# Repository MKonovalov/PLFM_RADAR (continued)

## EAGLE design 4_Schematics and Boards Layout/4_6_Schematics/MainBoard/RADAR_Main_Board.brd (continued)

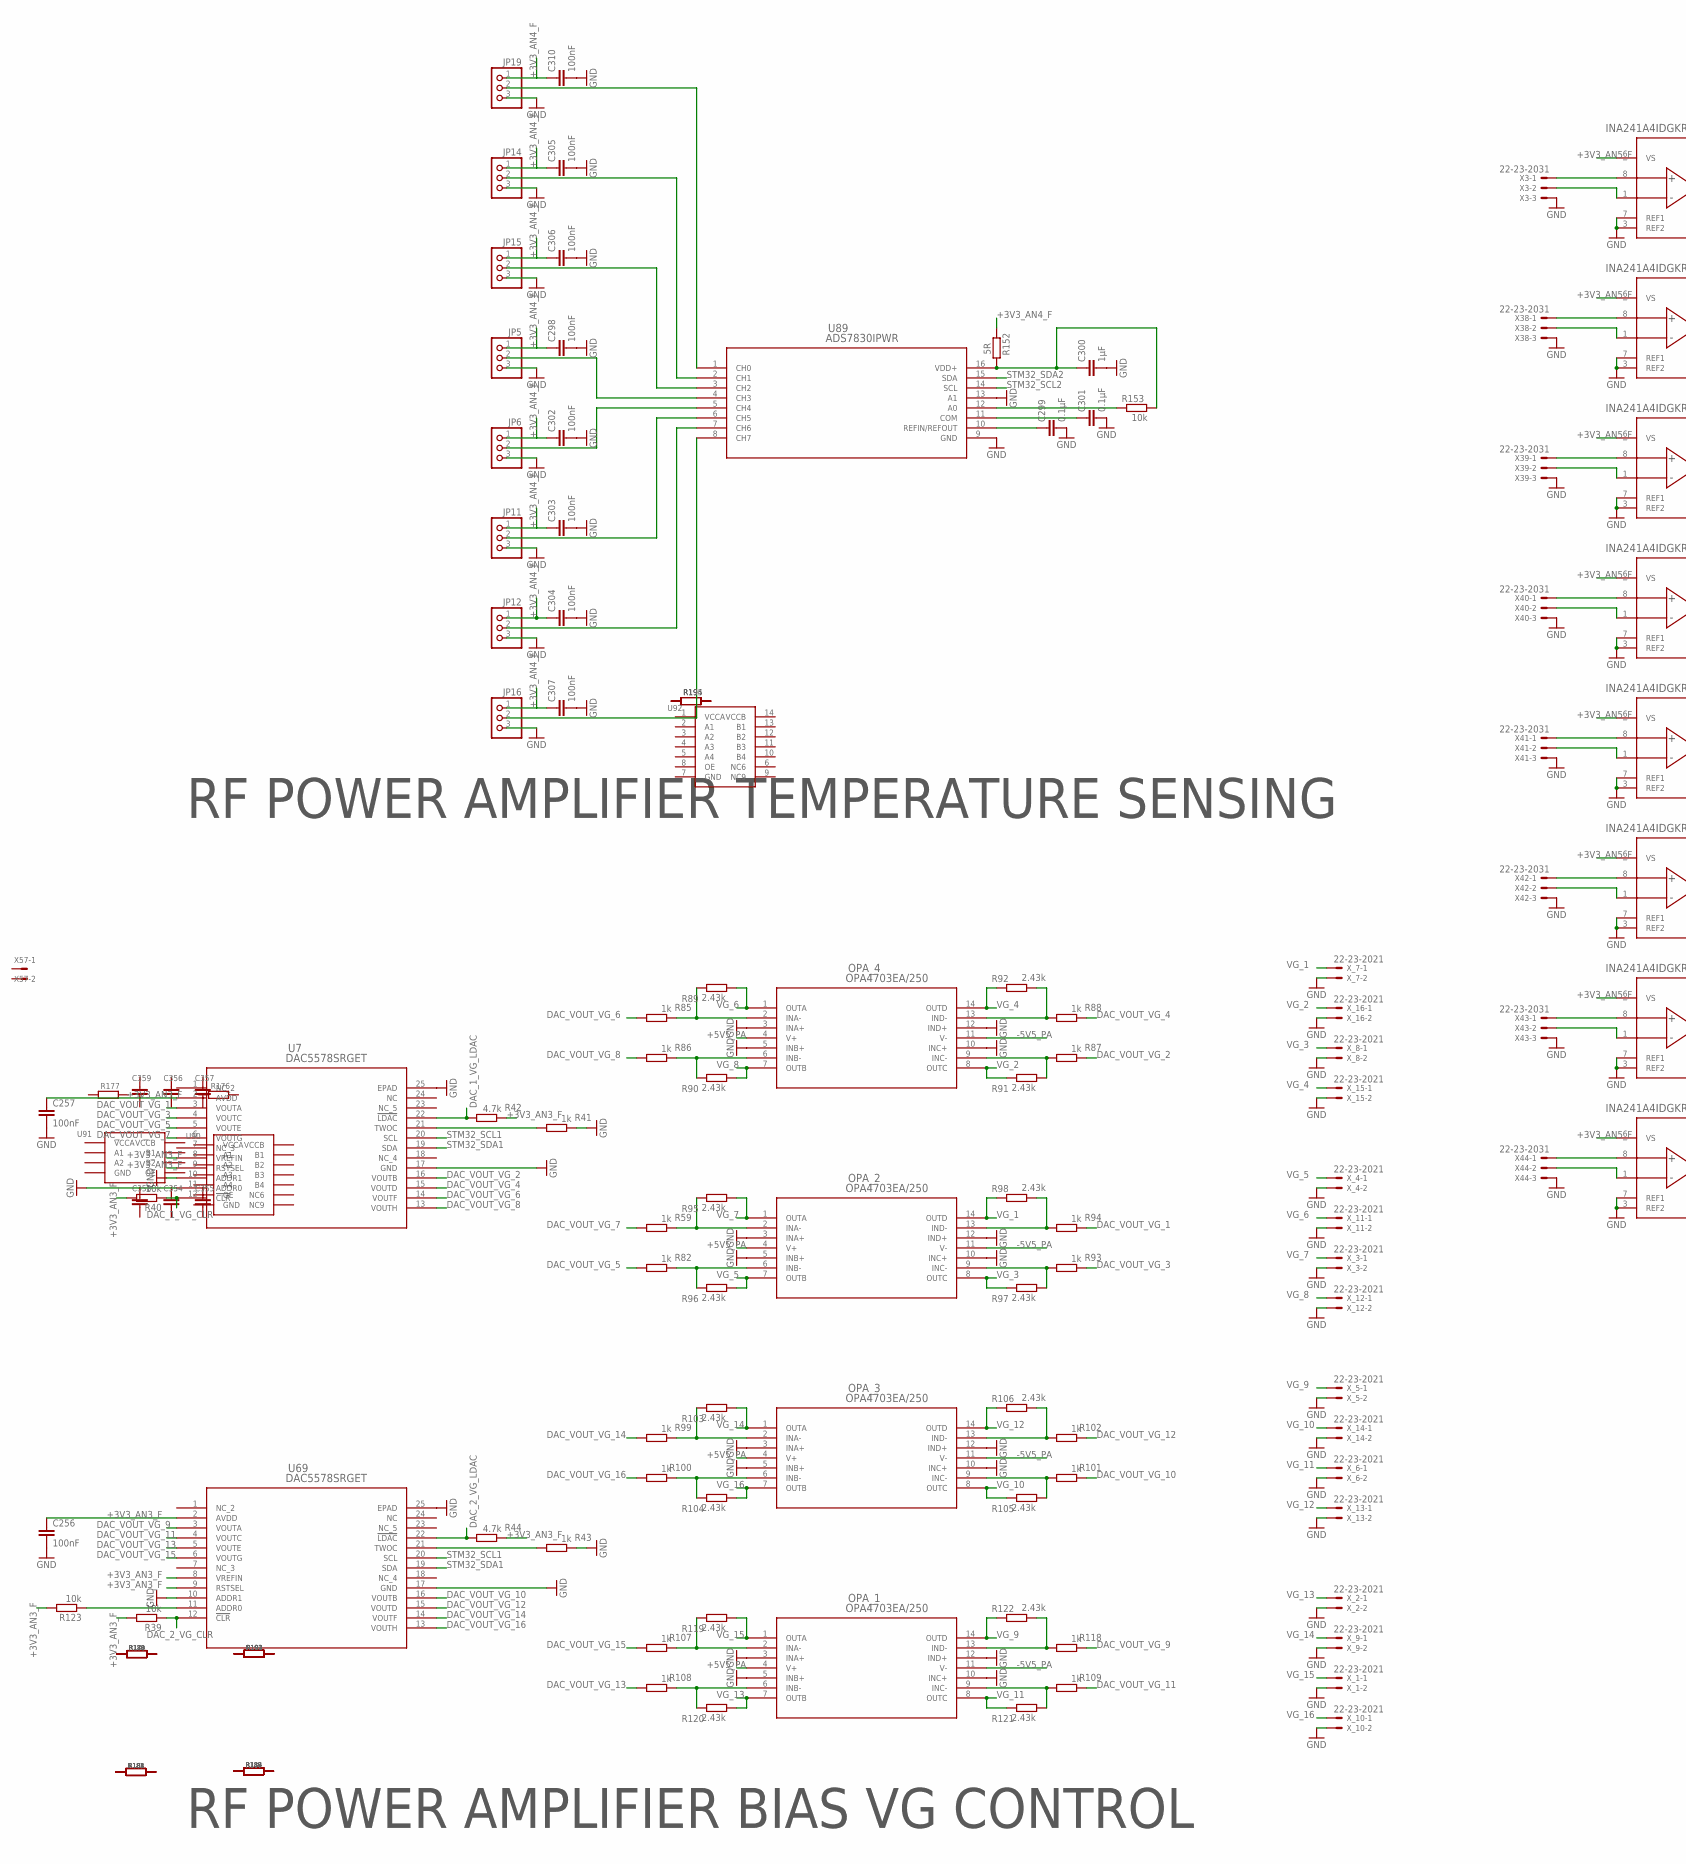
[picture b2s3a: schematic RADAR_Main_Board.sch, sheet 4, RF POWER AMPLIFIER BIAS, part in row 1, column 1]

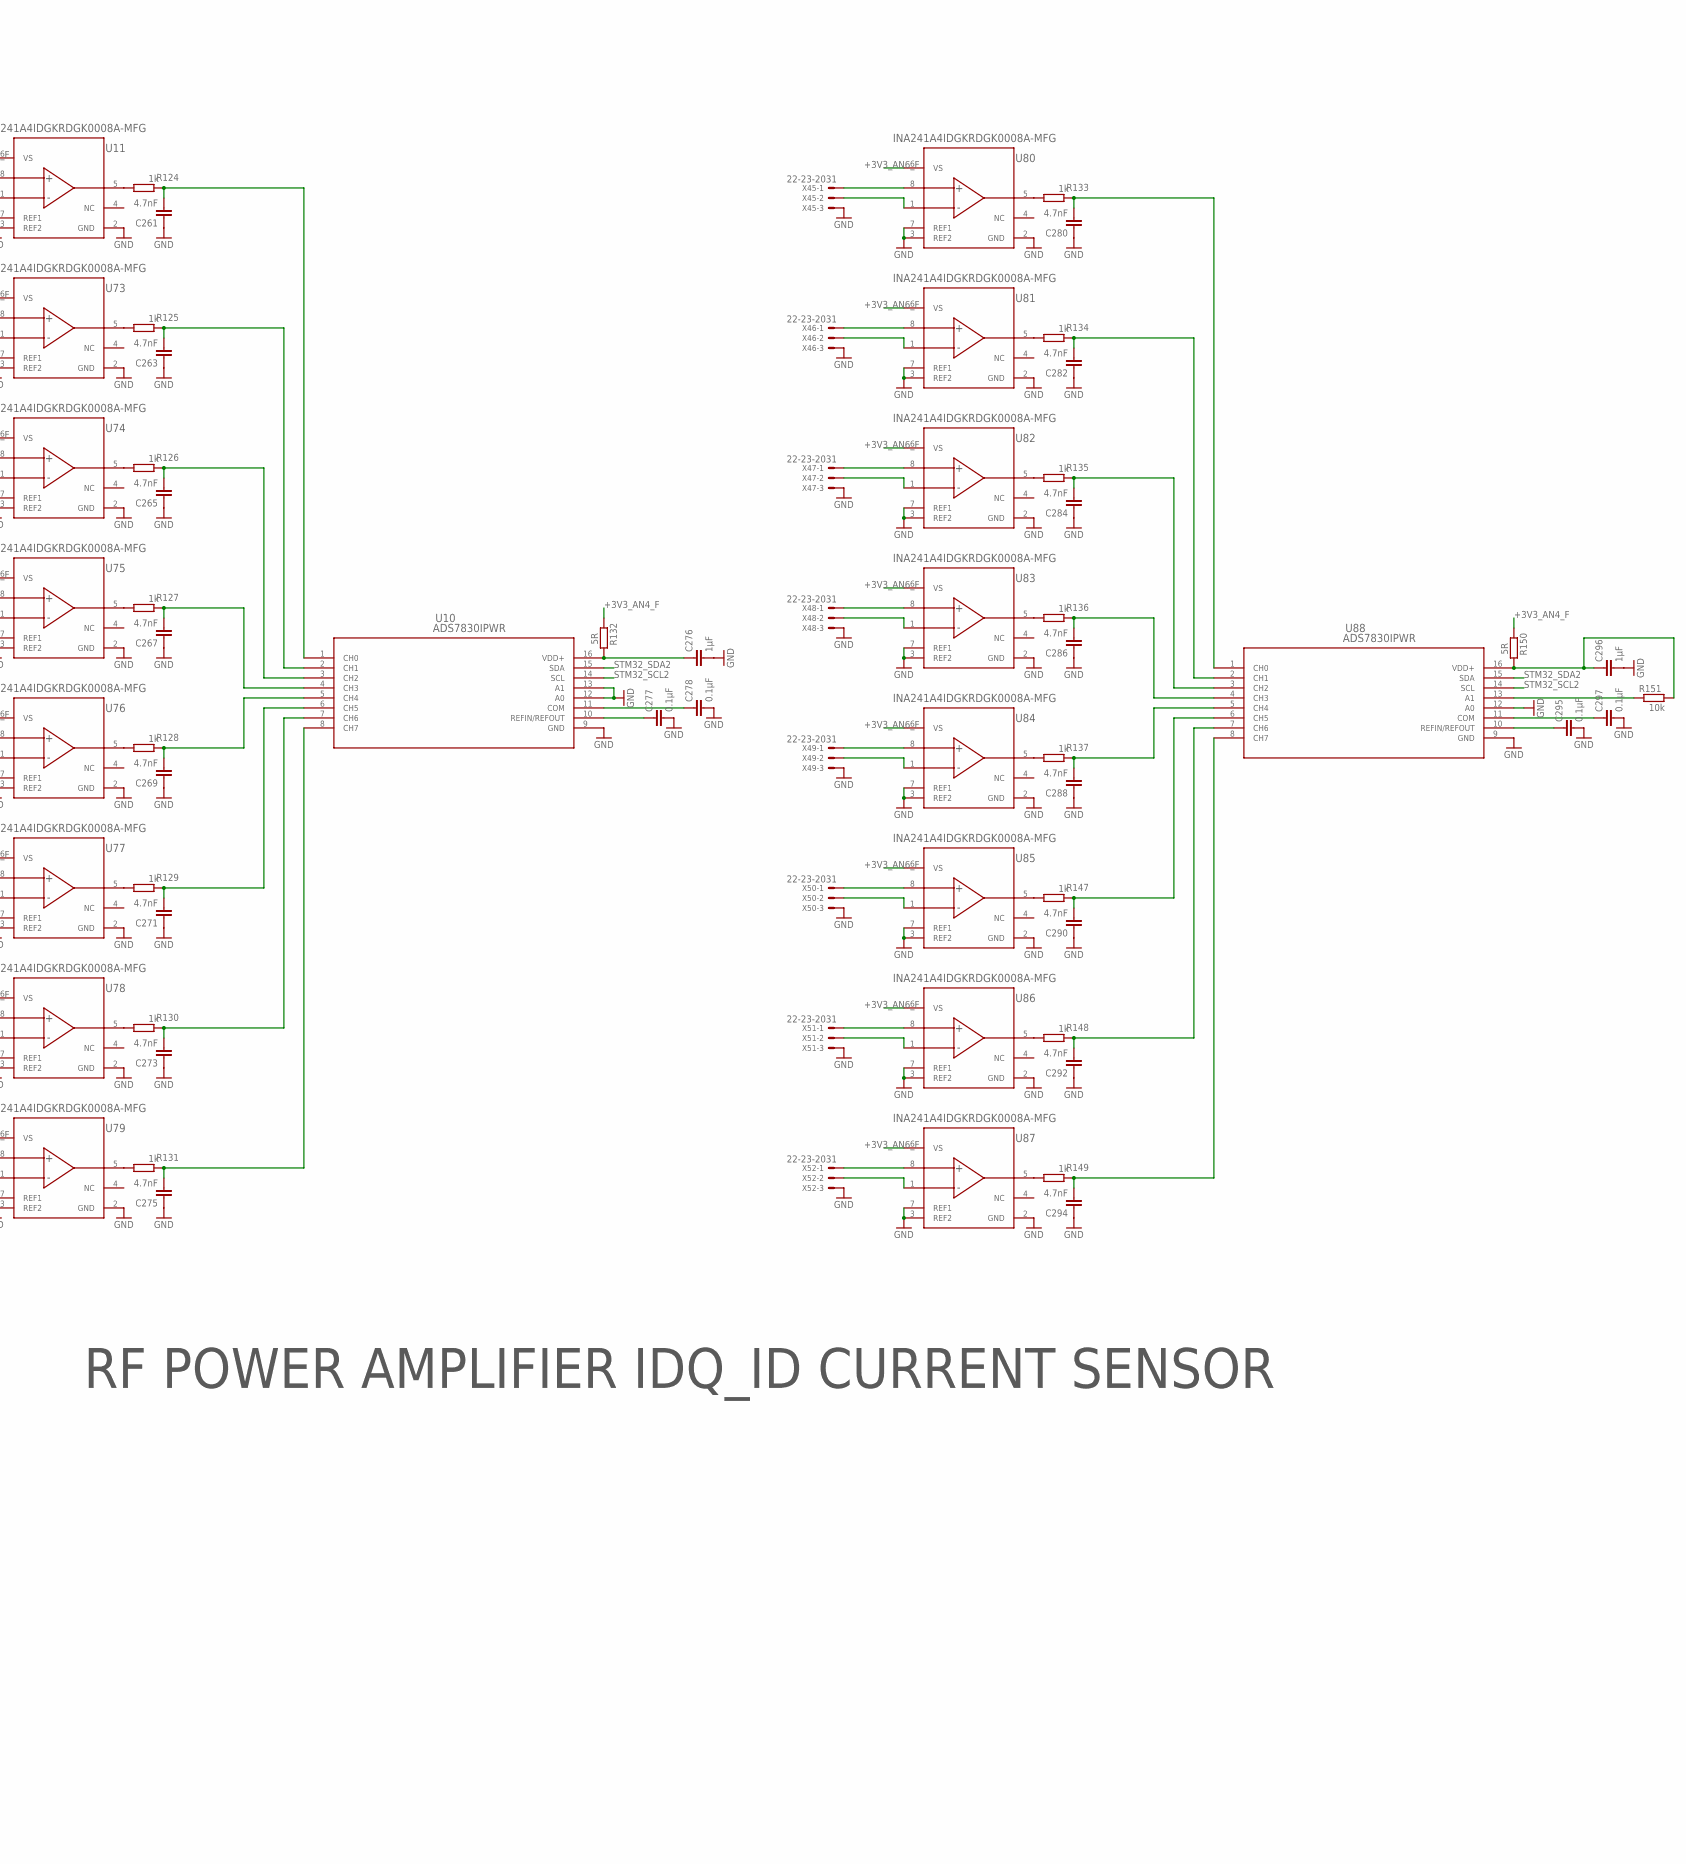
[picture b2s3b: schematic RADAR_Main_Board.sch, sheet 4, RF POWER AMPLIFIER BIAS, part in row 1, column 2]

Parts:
C256, C257, C298, C302, C303, C304, C305, C306, C307, C310: 100nF; C0201
C261, C263, C265, C267, C269, C271, C273, C275, C280, C282, C284, C286, C288, C290, C292, C294: 4.7nF; C0201
C276, C296, C300: 1µF; C0201
C277, C278, C295, C297, C299, C301: 0.1µF; C0201
C354, C355, C356, C357, C358, C359: 0.1uF; C0201
JP5, JP6, JP11, JP12, JP14, JP15, JP16, JP19: PINHD-1X3; 1X03
OPA_1, OPA_2, OPA_3, OPA_4: OPA4703EA/250; PW14
R39, R40, R123, R151, R153, R176, R177, R178, R179, R180, R181, R182, R183, R184, R185, R186, R187, R188, R189, R190, R191, R192, R193, R194: 10k; R0201
R41, R43, R59, R82, R85, R86, R87, R88, R93, R94, R99, R100, R101, R102, R107, R108, R109, R118, R124, R125, R126, R127, R128, R129, R130, R131, R133, R134, R135, R136, R137, R147, R148, R149: 1k; R0201
R42, R44, R195: 4.7k; R0201
R89, R90, R91, R92, R95, R96, R97, R98, R103, R104, R105, R106, R119, R120, R121, R122: 2.43k; R0201
R132, R150, R152: 5R; R0201
U7, U69: DAC5578SRGET; RGE24_2P7X2P7
U10, U88, U89: ADS7830IPWR; PW16
U11, U73, U74, U75, U76, U77, U78, U79, U80, U81, U82, U83, U84, U85, U86, U87: INA241A4IDGKRDGK0008A-MFG; DGK0008A-MFG
U92: TXS0104EPWR; PW0014A-MFG
X3, X38, X39, X40, X41, X42, X43, X44, X45, X46, X47, X48, X49, X50, X51, X52: 22-23-2031
X_1, X_2, X_3, X_4, X_5, X_6, X_7, X_8, X_9, X_10, X_11, X_12, X_13, X_14, X_15, X_16: 22-23-2021

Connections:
+1V8_FPGA: U92.VCCA; also elsewhere on the board
+3V3: U92.VCCB; also elsewhere on the board
+3V3_AN3_F: C256.1, C257.1, R39.2, R40.2, R42.1, R44.1, R123.2, U7.2 (AVDD), U7.8 (VREFIN), U7.9 (RSTSEL), U69.2 (AVDD), U69.8 (VREFIN), U69.9 (RSTSEL); also elsewhere on the board
+3V3_AN4_F: C298.1, C302.1, C303.1, C304.1, C305.1, C306.1, C307.1, C310.1, JP5.1, JP6.1, JP11.1, JP12.1, JP14.1, JP15.1, JP16.1, JP19.1, R132.1, R150.1, R152.1; also elsewhere on the board
+3V3_AN5_F: U11.6 (VS), U73.6 (VS), U74.6 (VS), U75.6 (VS), U76.6 (VS), U77.6 (VS), U78.6 (VS), U79.6 (VS); also elsewhere on the board
+3V3_AN6_F: U80.6 (VS), U81.6 (VS), U82.6 (VS), U83.6 (VS), U84.6 (VS), U85.6 (VS), U86.6 (VS), U87.6 (VS); also elsewhere on the board
+5V5_PA: OPA_1.4 (V+), OPA_2.4 (V+), OPA_3.4 (V+), OPA_4.4 (V+); also elsewhere on the board
ADC_SPI_CSB: U92.A1; also elsewhere on the board
ADC_SPI_SDIO: U92.A3; also elsewhere on the board
DAC_1_VG_CLR: R40.1, U7.12 (!CLR); also elsewhere on the board
DAC_1_VG_LDAC: R42.2, U7.22 (!LDAC); also elsewhere on the board
DAC_2_VG_CLR: R39.1, U69.12 (!CLR); also elsewhere on the board
DAC_2_VG_LDAC: R44.2, U69.22 (!LDAC); also elsewhere on the board
DAC_VOUT_VG_1: R94.1, U7.3 (VOUTA)
DAC_VOUT_VG_2: R87.1, U7.16 (VOUTB)
DAC_VOUT_VG_3: R93.1, U7.4 (VOUTC)
DAC_VOUT_VG_4: R88.1, U7.15 (VOUTD)
DAC_VOUT_VG_5: R82.2, U7.5 (VOUTE)
DAC_VOUT_VG_6: R85.2, U7.14 (VOUTF)
DAC_VOUT_VG_7: R59.2, U7.6 (VOUTG)
DAC_VOUT_VG_8: R86.2, U7.13 (VOUTH)
DAC_VOUT_VG_9: R118.1, U69.3 (VOUTA)
DAC_VOUT_VG_10: R101.1, U69.16 (VOUTB)
DAC_VOUT_VG_11: R109.1, U69.4 (VOUTC)
DAC_VOUT_VG_12: R102.1, U69.15 (VOUTD)
DAC_VOUT_VG_13: R108.2, U69.5 (VOUTE)
DAC_VOUT_VG_14: R99.2, U69.14 (VOUTF)
DAC_VOUT_VG_15: R107.2, U69.6 (VOUTG)
DAC_VOUT_VG_16: R100.2, U69.13 (VOUTH)
MCU_ADC_CSB: U92.B1; also elsewhere on the board
MCU_ADC_SCLK: U92.B2; also elsewhere on the board
MCU_ADC_SDIO: U92.B3; also elsewhere on the board
unnamed: R123.1, U69.11 (ADDR0)
unnamed: R43.2, U69.21 (TWOC)
unnamed: OPA_4.2 (INA-), R85.1, R89.1
unnamed: U11.8 (IN+), X3.1
unnamed: OPA_4.6 (INB-), R86.1, R90.1
unnamed: U11.1 (IN-), X3.2
unnamed: R124.2, U11.5 (OUT)
unnamed: C261.2, R124.1, U10.1 (CH0)
unnamed: U73.8 (IN+), X38.1
unnamed: OPA_4.9 (INC-), R87.2, R91.2
unnamed: U73.1 (IN-), X38.2
unnamed: R125.2, U73.5 (OUT)
unnamed: OPA_4.13 (IND-), R88.2, R92.2
unnamed: C263.2, R125.1, U10.2 (CH1)
unnamed: U74.8 (IN+), X39.1
unnamed: U74.1 (IN-), X39.2
unnamed: R126.2, U74.5 (OUT)
unnamed: R41.2, U7.21 (TWOC)
unnamed: OPA_2.2 (INA-), R59.1, R95.1
unnamed: C265.2, R126.1, U10.3 (CH2)
unnamed: OPA_2.6 (INB-), R82.1, R96.1
unnamed: U75.8 (IN+), X40.1
unnamed: U75.1 (IN-), X40.2
unnamed: R127.2, U75.5 (OUT)
unnamed: OPA_2.9 (INC-), R93.2, R97.2
unnamed: C267.2, R127.1, U10.4 (CH3)
unnamed: U76.8 (IN+), X41.1
unnamed: OPA_2.13 (IND-), R94.2, R98.2
unnamed: U76.1 (IN-), X41.2
unnamed: R128.2, U76.5 (OUT)
unnamed: C269.2, R128.1, U10.5 (CH4)
unnamed: U77.8 (IN+), X42.1
unnamed: U77.1 (IN-), X42.2
unnamed: R129.2, U77.5 (OUT)
unnamed: OPA_3.2 (INA-), R99.1, R103.1
unnamed: C271.2, R129.1, U10.6 (CH5)
unnamed: OPA_3.6 (INB-), R100.1, R104.1
unnamed: U78.8 (IN+), X43.1
unnamed: U78.1 (IN-), X43.2
unnamed: R130.2, U78.5 (OUT)
unnamed: OPA_3.9 (INC-), R101.2, R105.2
unnamed: C273.2, R130.1, U10.7 (CH6)
unnamed: U79.8 (IN+), X44.1
unnamed: OPA_3.13 (IND-), R102.2, R106.2
unnamed: U79.1 (IN-), X44.2
unnamed: R131.2, U79.5 (OUT)
unnamed: C275.2, R131.1, U10.8 (CH7)
unnamed: C277.1, U10.10 (REFIN/REFOUT)
unnamed: C276.1, R132.2, U10.16 (VDD+)
unnamed: C278.1, U10.11 (COM)
unnamed: OPA_1.2 (INA-), R107.1, R119.1
unnamed: U80.8 (IN+), X45.1
unnamed: OPA_1.6 (INB-), R108.1, R120.1
unnamed: U80.1 (IN-), X45.2
unnamed: R133.2, U80.5 (OUT)
unnamed: C280.2, R133.1, U88.1 (CH0)
unnamed: OPA_1.9 (INC-), R109.2, R121.2
unnamed: U81.8 (IN+), X46.1
unnamed: U81.1 (IN-), X46.2
unnamed: OPA_1.13 (IND-), R118.2, R122.2
unnamed: R134.2, U81.5 (OUT)
unnamed: C282.2, R134.1, U88.2 (CH1)
unnamed: U82.8 (IN+), X47.1
unnamed: U82.1 (IN-), X47.2
unnamed: R135.2, U82.5 (OUT)
unnamed: C284.2, R135.1, U88.3 (CH2)
unnamed: U83.8 (IN+), X48.1
unnamed: U83.1 (IN-), X48.2
unnamed: R136.2, U83.5 (OUT)
unnamed: C286.2, R136.1, U88.4 (CH3)
unnamed: U84.8 (IN+), X49.1
unnamed: U84.1 (IN-), X49.2
unnamed: R137.2, U84.5 (OUT)
unnamed: C288.2, R137.1, U88.5 (CH4)
unnamed: U85.8 (IN+), X50.1
unnamed: U85.1 (IN-), X50.2
unnamed: R147.2, U85.5 (OUT)
unnamed: C290.2, R147.1, U88.6 (CH5)
unnamed: U86.8 (IN+), X51.1
unnamed: U86.1 (IN-), X51.2
unnamed: R148.2, U86.5 (OUT)
unnamed: C292.2, R148.1, U88.7 (CH6)
unnamed: U87.8 (IN+), X52.1
unnamed: U87.1 (IN-), X52.2
unnamed: R149.2, U87.5 (OUT)
unnamed: C294.2, R149.1, U88.8 (CH7)
unnamed: C295.1, U88.10 (REFIN/REFOUT)
unnamed: C296.1, R150.2, R151.2, U88.16 (VDD+)
unnamed: C297.1, U88.11 (COM)
unnamed: R151.1, U88.13 (A1)
unnamed: R153.1, U89.12 (A0)
unnamed: C299.1, U89.10 (REFIN/REFOUT)
unnamed: C300.1, R152.2, R153.2, U89.16 (VDD+)
unnamed: C301.1, U89.11 (COM)
N$U92_OE: U92.OE; also elsewhere on the board
STM32_SCL1: U7.20 (SCL), U69.20 (SCL); also elsewhere on the board
STM32_SCL2: U10.14 (SCL), U88.14 (SCL), U89.14 (SCL); also elsewhere on the board
STM32_SDA1: U7.19 (SDA), U69.19 (SDA); also elsewhere on the board
STM32_SDA2: U10.15 (SDA), U88.15 (SDA), U89.15 (SDA); also elsewhere on the board
TEMP_1: JP19.2, U89.1 (CH0); also elsewhere on the board
TEMP_2: JP14.2, U89.2 (CH1); also elsewhere on the board
TEMP_3: JP15.2, U89.3 (CH2); also elsewhere on the board
TEMP_4: JP5.2, U89.4 (CH3); also elsewhere on the board
TEMP_5: JP6.2, U89.5 (CH4); also elsewhere on the board
TEMP_6: JP11.2, U89.6 (CH5); also elsewhere on the board
TEMP_7: JP12.2, U89.7 (CH6); also elsewhere on the board
TEMP_8: JP16.2, U89.8 (CH7); also elsewhere on the board
VG_1: OPA_2.14 (OUTD), R98.1, R178.1, X_7.1
VG_2: OPA_4.8 (OUTC), R91.1, R190.1, X_16.1
VG_3: OPA_2.8 (OUTC), R97.1, R179.1, X_8.1
VG_4: OPA_4.14 (OUTD), R92.1, R191.1, X_15.1
VG_5: OPA_2.7 (OUTB), R96.2, R180.1, X_4.1
VG_6: OPA_4.1 (OUTA), R89.2, R192.1, X_11.1
VG_7: OPA_2.1 (OUTA), R95.2, R181.1, X_3.1
VG_8: OPA_4.7 (OUTB), R90.2, R193.1, X_12.1
VG_9: OPA_1.14 (OUTD), R122.1, R182.1, X_5.1
VG_10: OPA_3.8 (OUTC), R105.1, R186.1, X_14.1
VG_11: OPA_1.8 (OUTC), R121.1, R183.1, X_6.1
VG_12: OPA_3.14 (OUTD), R106.1, R187.1, X_13.1
VG_13: OPA_1.7 (OUTB), R120.2, R184.1, X_2.1
VG_14: OPA_3.1 (OUTA), R103.2, R188.1, X_9.1
VG_15: OPA_1.1 (OUTA), R119.2, R185.1, X_1.1
VG_16: OPA_3.7 (OUTB), R104.2, R189.1, X_10.1

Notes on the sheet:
RF POWER AMPLIFIER IDQ_ID CURRENT SENSOR
RF POWER AMPLIFIER BIAS VG CONTROL
RF POWER AMPLIFIER TEMPERATURE SENSING

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
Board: 10 copper layers, 836 parts (0 on the bottom side), 668 nets.

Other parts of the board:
R196, R197, R198, R199, R200, R201, R202, R203: 10k; R0201
U90: TXS0104EPWR; PW0014A-MFG
U91: TXS0102DCUR; DCU0008A-MFG
X5, X7, X14: 22-23-2041
X6, X11, X13, X15, X19, X22: 22-23-2031
X25, X26, X27, X57: 22-23-2021

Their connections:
+2V5_FPGA: U90.1, U91.3, X57.1; also elsewhere on the board
+3V3_AN4_F: R196.2, R197.2, R198.2, R199.2, R200.2, R201.2, R202.2, R203.2; also elsewhere on the board
+3V3_FPGA: U90.14, U91.7; also elsewhere on the board
+5V0_PA_1: X14.1; also elsewhere on the board
+5V0_PA_2: X5.1; also elsewhere on the board
+5V0_PA_3: X7.1; also elsewhere on the board
-3V3_SW: X6.1; also elsewhere on the board
-3V4: X11.1, X22.1; also elsewhere on the board
-5V0_ADAR12: X13.1; also elsewhere on the board
-5V0_ADAR34: X15.1; also elsewhere on the board
-5V5_PA: X19.1; also elsewhere on the board
FLASH_DQ0_F: U90.13; also elsewhere on the board
FLASH_DQ1_F: U90.12; also elsewhere on the board
FLASH_DQ2_F: U90.11; also elsewhere on the board
FLASH_DQ3_F: U90.10; also elsewhere on the board
FLASH_NCS_F: U91.8; also elsewhere on the board
FLASH_NRST_F: U91.1; also elsewhere on the board
FPGA_FLASH_DQ0: U90.2; also elsewhere on the board
FPGA_FLASH_DQ1: U90.3; also elsewhere on the board
FPGA_FLASH_DQ2: U90.4; also elsewhere on the board
FPGA_FLASH_DQ3: U90.5; also elsewhere on the board
FPGA_FLASH_NCS: U91.5; also elsewhere on the board
FPGA_FLASH_NRST: U91.4; also elsewhere on the board
N$U90_OE: U90.8; also elsewhere on the board
N$U91_OE: U91.6; also elsewhere on the board
PG_2V5_FPGA: X27.1; also elsewhere on the board
PG_3V3_ADTR: X25.1; also elsewhere on the board
PG_3V3_XO: X26.1; also elsewhere on the board
TEMP_1: R196.1; also elsewhere on the board
TEMP_2: R197.1; also elsewhere on the board
TEMP_3: R198.1; also elsewhere on the board
TEMP_4: R199.1; also elsewhere on the board
TEMP_5: R200.1; also elsewhere on the board
TEMP_6: R201.1; also elsewhere on the board
TEMP_7: R202.1; also elsewhere on the board
TEMP_8: R203.1; also elsewhere on the board

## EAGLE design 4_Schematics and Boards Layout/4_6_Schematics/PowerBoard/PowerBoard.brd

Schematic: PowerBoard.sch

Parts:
C1, C6, C12, C18, C29, C30, C36, C42, C54, C60, C66, C71, C76, C77, C83, C89, C109, C119, C129, C144, C154: 0.1µF; C0805
C2, C3, C7, C8, C11, C13, C14, C17, C19, C20, C23, C31, C32, C35, C37, C38, C41, C43, C44, C47, C48, C49, C55, C56, C59, C61, C62, C65, C67, C68, C72, C73, C78, C79, C82, C84, C85, C88, C90, C91, C110, C111, C120, C121, C130, C131, C145, C146, C149, C155, C156, C159, C164, C165, C169, C170, C171, C172: 22µF; C0603
C4, C5, C9, C10, C15, C16, C21, C22, C24, C25, C28, C33, C34, C39, C40, C45, C46, C50, C51, C52, C53, C57, C58, C63, C64, C69, C70, C74, C75, C80, C81, C86, C87, C92, C93, C94, C95, C108, C112, C113, C114, C115, C118, C122, C123, C124, C125, C128, C132, C133, C134, C135, C138, C139, C140, C143, C147, C148, C157, C158: 10µF; C0805
C26, C27, C106, C107, C116, C117, C126, C127, C136, C137, C141, C142: 1µF; C0805
C96, C97, C98, C99, C100, C101, C102, C103, C104, C105, C173, C174: T521W476M020ATE045; T521W
C150, C152, C160, C162, C167, C168: 10nF; C0603
C151, C153, C161, C163, C166: 10µF; C0603
R1: 3.09k; M0805
R2, R4, R6, R8, R10, R12, R14, R16, R18, R20, R22, R24, R26, R28, R30, R32, R34, R36, R38, R40, R42, R44, R46, R48, R50, R52, R56, R61, R62, R63: 10k; M0805
R3: 13.7k; M0805
R5, R7, R11, R13, R15, R19: 32.2k; M0805
R9, R35, R43, R47: 12k; M0805
R17, R23, R25, R27, R29, R31, R37, R41, R45, R51, R55: 56.2k; M0805
R21: 34.8k; M0805
R33: 61.9k; M0805
R39: 2k; M0805
R49: 23.4k; M0805
R53, R57: 35.7k; M0805
R54, R58, R60: 11.5k; M0805
R59: 24.3k; M0805
SV1: MA10-2
TP1, TP2, TP3, TP4, TP5, TP6, TP7, TP8, TP9, TP10, TP11, TP12, TP13, TP14, TP15: S1751-46
U1, U2, U3, U4, U6, U7, U8, U9, U10, U11, U12, U13, U14, U15, U16, U17, U24, U26, U28, U31, U33: TPS562208DDCT; DDC0006A_N
U5, U23, U25, U27, U29, U30: ADM7151ACPZ-04-R7; CP_8_11_ADI
U18, U19, U20, U21, U22: LM2662MX/NOPB; M08A
U32, U34, U35: TPS7A8300RGRR; RGR20_2P05X2P05_TEX
U$1, U$2: 2.2µH; IND_VLP8040T-1R0N_TDK
U$3, U$4, U$5, U$6, U$7, U$8, U$9, U$10, U$11, U$12, U$13, U$14, U$15, U$16, U$17, U$18, U$19, U$20, U$21: 3.3µH; IND_VLP8040T-1R0N_TDK
X1: AK300/2
X2, X3, X4, X5, X6, X7, X8, X9, X10, X11, X12, X13, X14, X15, X16, X17, X22, X23, X25, X26, X27, X28, X29, X30, X34, X35: 22-23-2021

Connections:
+1V0_FPGA: C2.1, C3.1, R1.2, TP1.1, TP1.2, U$1.1, X4.1
+1V8_CLOCK: C115.2, U25.2 (VOUT), X10.1
+1V8_FPGA: C7.1, C8.1, C11.1, R3.2, TP2.1, TP2.2, U$2.1, X5.1
+2V5_FPGA: C165.1, R59.1, TP3.1, TP3.2, U35.1 (OUT_2), U35.19 (OUT_3), U35.20 (OUT); also elsewhere on the board
+3V3: C13.1, C14.1, C17.1, R5.2, R61.2, R62.2, R63.2, TP4.1, TP4.2, U$3.1, X16.1
+3V3_ADAR12: C31.1, C32.1, C35.1, R11.2, TP8.1, TP8.2, U$6.1, X14.1
+3V3_ADAR34: C37.1, C38.1, C41.1, R13.2, U$7.1, X15.1
+3V3_ADTR: C149.1, R53.2, TP6.1, TP6.2, U32.1 (OUT_2), U32.19 (OUT_3), U32.20 (OUT), X34.1
+3V3_AN: C25.2, TP5.1, TP5.2, U5.2 (VOUT), X12.1
+3V3_CLOCK: C53.2, U23.2 (VOUT), X11.1
+3V3_FPGA: C19.1, C20.1, C23.1, R7.2, U$4.1, X27.1
+3V3_LO_1: C125.2, U27.2 (VOUT), X8.1
+3V3_LO_2: C135.2, U29.2 (VOUT), X7.1
+3V3_SW: C55.1, C56.1, C59.1, R19.2, U18.8 (V+), U$10.1, X29.1
+3V3_VDD_SW: C43.1, C44.1, C47.1, R15.2, U$8.1, X30.1
+3V3_XO: C159.1, C169.1, C170.1, C171.1, C172.1, R57.2, TP7.1, TP7.2, U34.1 (OUT_2), U34.19 (OUT_3), U34.20 (OUT), X35.1
+3V4: C61.1, C62.1, C65.1, R21.2, TP10.1, TP10.2, U19.8 (V+), U$11.1, X23.1
+5V0_0: C28.2, C67.1, C68.1, R23.2, U5.7 (EN), U5.8 (VIN), U$12.1, X22.1
+5V0_1: C48.1, C49.1, C108.2, R17.2, U23.8 (VIN), U$5.1, X2.1
+5V0_2: C110.1, C111.1, C118.2, R37.2, U25.8 (VIN), U$9.1, X9.1
+5V0_3: C120.1, C121.1, C128.2, R41.2, U27.7 (EN), U27.8 (VIN), U$18.1, X17.1
+5V0_4: C130.1, C131.1, C138.2, R45.2, U29.7 (EN), U29.8 (VIN), U$19.1, X25.1
+5V0_5: C155.1, C156.1, C163.1, C164.1, R55.2, U34.14 (EN), U34.15 (IN_2), U34.16 (IN_3), U34.17 (IN), U35.14 (EN), U35.15 (IN_2), U35.16 (IN_3), U35.17 (IN), U$21.1, X28.1
+5V0_ADAR: C72.1, C73.1, R25.2, U20.8 (V+), U21.8 (V+), U$13.1, X13.1; also elsewhere on the board
+5V0_ADTR: C145.1, C146.1, C153.1, R51.2, U32.15 (IN_2), U32.16 (IN_3), U32.17 (IN), U$20.1, X26.1
+5V0_LO: C140.2, U30.2 (VOUT), X6.1; also elsewhere on the board
+5V0_PA_1: C78.1, C79.1, R27.2, U$14.1; also elsewhere on the board
+5V0_PA_2: C84.1, C85.1, R29.2, U$15.1; also elsewhere on the board
+5V0_PA_3: C90.1, C91.1, R31.2, U$16.1; also elsewhere on the board
+5V5_PA: C82.1, C88.1, R33.2, TP12.1, TP12.2, U22.8 (V+), U$17.1, X3.1
-3V3_SW: C97.2 (-), U18.5 (OUT); also elsewhere on the board
-3V4: C99.2 (-), TP11.1, TP11.2, U19.5 (OUT); also elsewhere on the board
-5V0_ADAR12: C101.2 (-), TP9.1, TP9.2, U20.5 (OUT); also elsewhere on the board
-5V0_ADAR34: C103.2 (-), U21.5 (OUT); also elsewhere on the board
-5V5_PA: C105.2 (-), U22.5 (OUT); also elsewhere on the board
EN_+1V0_FPGA: SV1.1, U1.5 (EN)
EN_+1V8_CLOCK: SV1.8, U25.7 (EN)
EN_+1V8_FPGA: SV1.3, U2.5 (EN)
EN_+3V3_ADAR12: SV1.9, U6.5 (EN)
EN_+3V3_ADAR34: SV1.11, U7.5 (EN)
EN_+3V3_ADTR: SV1.13, U32.14 (EN)
EN_+3V3_CLOCK: SV1.10, U23.7 (EN)
EN_+3V3_FPGA: SV1.5, U4.5 (EN)
EN_+3V3_SW: SV1.15, U10.5 (EN)
EN_+3V3_VDD_SW: SV1.17, U8.5 (EN)
EN_+5V0_ADAR: SV1.7, U13.5 (EN)
EN_+5V0_PA1: SV1.19, U14.5 (EN)
EN_+5V0_PA2: SV1.2, U15.5 (EN)
EN_+5V0_PA3: SV1.4, U16.5 (EN)
EN_+5V5_PA: SV1.6, U17.5 (EN)
GND: C2.2, C3.2, C4.2, C5.2, C7.2, C8.2, C9.2, C10.2, C11.2, C13.2, C14.2, C15.2, C16.2, C17.2, C19.2, C20.2, C21.2, C22.2, C23.2, C24.1, C25.1, C26.1, C27.1, C28.1, C31.2, C32.2, C33.2, C34.2, C35.2, C37.2, C38.2, C39.2, C40.2, C41.2, C43.2, C44.2, C45.2, C46.2, C47.2, C48.2, C49.2, C50.2, C51.2, C52.1, C53.1, C55.2, C56.2, C57.2, C58.2, C59.2, C61.2, C62.2, C63.2, C64.2, C65.2, C67.2, C68.2, C69.2, C70.2, C72.2, C73.2, C74.2, C75.2, C78.2, C79.2, C80.2, C81.2, C82.2, C84.2, C85.2, C86.2, C87.2, C88.2, C90.2, C91.2, C92.2, C93.2, C94.2, C95.2, C97.1 (+), C99.1 (+), C101.1 (+), C103.1 (+), C105.1 (+), C106.1, C107.1, C108.1, C110.2, C111.2, C112.2, C113.2, C114.1, C115.1, C116.1, C117.1, C118.1, C120.2, C121.2, C122.2, C123.2, C124.1, C125.1, C126.1, C127.1, C128.1, C130.2, C131.2, C132.2, C133.2, C134.1, C135.1, C136.1, C137.1, C138.1, C139.1, C140.1, C141.1, C142.1, C143.1, C145.2, C146.2, C147.2, C148.2, C149.2, C151.2, C152.2, C153.2, C155.2, C156.2, C157.2, C158.2, C159.2, C161.2, C162.2, C163.2, C164.2, C165.2, C166.2, C167.2, C169.2, C170.2, C171.2, C172.2, R2.1, R4.1, R6.1, R8.1, R10.1, R12.1, R14.1, R16.1, R18.1, R20.1, R22.1, R24.1, R26.1, R28.1, R30.1, R32.1, R34.1, R36.1, R38.1, R40.1, R42.1, R44.1, R46.1, R48.1, R50.1, R52.1, R54.1, R56.1, R58.1, R60.2, SV1.12, SV1.14, SV1.16, SV1.18, SV1.20, U1.1 (GND), U2.1 (GND), U3.1 (GND), U4.1 (GND), U5.4 (GND), U5.9 (EPAD), U6.1 (GND), U7.1 (GND), U8.1 (GND), U9.1 (GND), U10.1 (GND), U11.1 (GND), U12.1 (GND), U13.1 (GND), U14.1 (GND), U15.1 (GND), U16.1 (GND), U17.1 (GND), U18.3 (GND), U18.6 (LV), U19.3 (GND), U19.6 (LV), U20.3 (GND), U20.6 (LV), U21.3 (GND), U21.6 (LV), U22.3 (GND), U22.6 (LV), U23.4 (GND), U23.9 (EPAD), U24.1 (GND), U25.4 (GND), U25.9 (EPAD), U26.1 (GND), U27.4 (GND), U27.9 (EPAD), U28.1 (GND), U29.4 (GND), U29.9 (EPAD), U30.4 (GND), U30.9 (EPAD), U31.1 (GND), U32.8 (GND_2), U32.18 (GND), U32.21 (EPAD), U33.1 (GND), U34.8 (GND_2), U34.18 (GND), U34.21 (EPAD), U35.8 (GND_2), U35.18 (GND), U35.21 (EPAD), X1.2, X2.2, X3.2, X4.2, X5.2, X6.2, X7.2, X8.2, X9.2, X10.2, X11.2, X12.2, X13.2, X14.2, X15.2, X16.2, X17.2, X22.2, X23.2, X25.2, X26.2, X27.2, X28.2, X29.2, X30.2, X34.2, X35.2; also elsewhere on the board
unnamed: C1.2, U1.2 (SW), U$1.2
unnamed: C1.1, U1.6 (VBST)
unnamed: C166.1, U35.12 (BIAS)
unnamed: C168.2, R59.2, R60.1, U35.3 (FB)
unnamed: C167.1, U35.13 (NR/SS)
unnamed: C168.1, U35.2 (SNS)
unnamed: C6.2, U2.2 (SW), U$2.2
unnamed: R1.1, R2.2, U1.4 (VFB)
unnamed: C6.1, U2.6 (VBST)
unnamed: R3.1, R4.2, U2.4 (VFB)
unnamed: C12.2, U3.2 (SW), U$3.2
unnamed: C12.1, U3.6 (VBST)
unnamed: R5.1, R6.2, U3.4 (VFB)
unnamed: C18.2, U4.2 (SW), U$4.2
unnamed: C18.1, U4.6 (VBST)
unnamed: R7.1, R8.2, U4.4 (VFB)
unnamed: C24.2, U5.1 (VREG)
unnamed: C139.2, U30.1 (VREG)
unnamed: C26.2, U5.3 (BYP)
unnamed: C30.2, U6.2 (SW), U$6.2
unnamed: C30.1, U6.6 (VBST)
unnamed: R11.1, R12.2, U6.4 (VFB)
unnamed: C36.2, U7.2 (SW), U$7.2
unnamed: C36.1, U7.6 (VBST)
unnamed: R13.1, R14.2, U7.4 (VFB)
unnamed: C42.2, U8.2 (SW), U$8.2
unnamed: C42.1, U8.6 (VBST)
unnamed: R15.1, R16.2, U8.4 (VFB)
unnamed: R9.1, R10.2, U5.5 (REF_SENSE)
unnamed: C29.2, U9.2 (SW), U$5.2
unnamed: C27.2, R9.2, U5.6 (REF)
unnamed: C54.2, U10.2 (SW), U$10.2
unnamed: C54.1, U10.6 (VBST)
unnamed: R19.1, R20.2, U10.4 (VFB)
unnamed: C60.2, U11.2 (SW), U$11.2
unnamed: C60.1, U11.6 (VBST)
unnamed: R21.1, R22.2, U11.4 (VFB)
unnamed: C66.2, U12.2 (SW), U$12.2
unnamed: C66.1, U12.6 (VBST)
unnamed: R23.1, R24.2, U12.4 (VFB)
unnamed: C71.2, U13.2 (SW), U$13.2
unnamed: C71.1, U13.6 (VBST)
unnamed: R25.1, R26.2, U13.4 (VFB)
unnamed: C77.2, U14.2 (SW), U$14.2
unnamed: C77.1, U14.6 (VBST)
unnamed: R27.1, R28.2, U14.4 (VFB)
unnamed: C83.2, U15.2 (SW), U$15.2
unnamed: C83.1, U15.6 (VBST)
unnamed: R29.1, R30.2, U15.4 (VFB)
unnamed: C89.2, U16.2 (SW), U$16.2
unnamed: C89.1, U16.6 (VBST)
unnamed: R31.1, R32.2, U16.4 (VFB)
unnamed: C76.2, U17.2 (SW), U$17.2
unnamed: C76.1, U17.6 (VBST)
unnamed: R33.1, R34.2, U17.4 (VFB)
unnamed: C98.1 (+), U19.2 (C1+)
unnamed: C98.2 (-), U19.4 (C1-)
unnamed: C96.1 (+), U18.2 (C1+)
unnamed: C96.2 (-), U18.4 (C1-)
unnamed: C100.1 (+), U20.2 (C1+)
unnamed: C100.2 (-), U20.4 (C1-)
unnamed: C102.1 (+), U21.2 (C1+)
unnamed: C102.2 (-), U21.4 (C1-)
unnamed: C104.1 (+), U22.2 (C1+)
unnamed: C104.2 (-), U22.4 (C1-)
unnamed: C141.2, U30.3 (BYP)
unnamed: R49.1, R50.2, U30.5 (REF_SENSE)
unnamed: C29.1, U9.6 (VBST)
unnamed: R17.1, R18.2, U9.4 (VFB)
unnamed: C52.2, U23.1 (VREG)
unnamed: C142.2, R49.2, U30.6 (REF)
unnamed: C106.2, U23.3 (BYP)
unnamed: R35.1, R36.2, U23.5 (REF_SENSE)
unnamed: C107.2, R35.2, U23.6 (REF)
unnamed: C144.2, U31.2 (SW), U$20.2
unnamed: C144.1, U31.6 (VBST)
unnamed: C109.2, U24.2 (SW), U$9.2
unnamed: C109.1, U24.6 (VBST)
unnamed: R37.1, R38.2, U24.4 (VFB)
unnamed: C114.2, U25.1 (VREG)
unnamed: R51.1, R52.2, U31.4 (VFB)
unnamed: C116.2, U25.3 (BYP)
unnamed: R39.1, R40.2, U25.5 (REF_SENSE)
unnamed: C117.2, R39.2, U25.6 (REF)
unnamed: C154.2, U33.2 (SW), U$21.2
unnamed: C150.1, U32.2 (SNS)
unnamed: C119.2, U26.2 (SW), U$18.2
unnamed: C119.1, U26.6 (VBST)
unnamed: R41.1, R42.2, U26.4 (VFB)
unnamed: C124.2, U27.1 (VREG)
unnamed: C154.1, U33.6 (VBST)
unnamed: C126.2, U27.3 (BYP)
unnamed: R43.1, R44.2, U27.5 (REF_SENSE)
unnamed: C127.2, R43.2, U27.6 (REF)
unnamed: C150.2, R53.1, R54.2, U32.3 (FB)
unnamed: C151.1, U32.12 (BIAS)
unnamed: C129.2, U28.2 (SW), U$19.2
unnamed: C129.1, U28.6 (VBST)
unnamed: R45.1, R46.2, U28.4 (VFB)
unnamed: C134.2, U29.1 (VREG)
unnamed: R55.1, R56.2, U33.4 (VFB)
unnamed: C136.2, U29.3 (BYP)
unnamed: R47.1, R48.2, U29.5 (REF_SENSE)
unnamed: C137.2, R47.2, U29.6 (REF)
unnamed: C152.1, U32.13 (NR/SS)
unnamed: C160.1, U34.2 (SNS)
unnamed: C160.2, R57.1, R58.2, U34.3 (FB)
unnamed: C161.1, U34.12 (BIAS)
unnamed: C162.1, U34.13 (NR/SS)
N$U36_C1M: C173.2 (-); also elsewhere on the board
N$U36_C1P: C173.1 (+); also elsewhere on the board
N$U37_C1M: C174.2 (-); also elsewhere on the board
N$U37_C1P: C174.1 (+); also elsewhere on the board
PG_2V5_FPGA: R63.1, TP15.1, TP15.2, U35.4 (PG); also elsewhere on the board
PG_3V3_ADTR: R61.1, TP13.1, TP13.2, U32.4 (PG); also elsewhere on the board
PG_3V3_XO: R62.1, TP14.1, TP14.2, U34.4 (PG); also elsewhere on the board
VIN: C4.1, C5.1, C9.1, C10.1, C15.1, C16.1, C21.1, C22.1, C33.1, C34.1, C39.1, C40.1, C45.1, C46.1, C50.1, C51.1, C57.1, C58.1, C63.1, C64.1, C69.1, C70.1, C74.1, C75.1, C80.1, C81.1, C86.1, C87.1, C92.1, C93.1, C94.1, C95.1, C112.1, C113.1, C122.1, C123.1, C132.1, C133.1, C143.2, C147.1, C148.1, C157.1, C158.1, U1.3 (VIN), U2.3 (VIN), U3.3 (VIN), U3.5 (EN), U4.3 (VIN), U6.3 (VIN), U7.3 (VIN), U8.3 (VIN), U9.3 (VIN), U9.5 (EN), U10.3 (VIN), U11.3 (VIN), U11.5 (EN), U12.3 (VIN), U12.5 (EN), U13.3 (VIN), U14.3 (VIN), U15.3 (VIN), U16.3 (VIN), U17.3 (VIN), U24.3 (VIN), U24.5 (EN), U26.3 (VIN), U26.5 (EN), U28.3 (VIN), U28.5 (EN), U30.7 (EN), U30.8 (VIN), U31.3 (VIN), U31.5 (EN), U33.3 (VIN), U33.5 (EN), X1.1

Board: 2 copper layers, 351 parts (0 on the bottom side), 168 nets.

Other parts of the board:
U36, U37: LM2662MX/NOPB; M08A
X18, X19, X20, X21, X24: 22-23-2031
X31, X32, X33: 22-23-2041
X36, X37, X38, X39, X40: 22-23-2021

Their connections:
+2V5_FPGA: X36.1; also elsewhere on the board
+5V0_ADAR: U36.8, U37.8; also elsewhere on the board
+5V0_LO: X37.1; also elsewhere on the board
+5V0_PA_1: X31.1; also elsewhere on the board
+5V0_PA_2: X32.1; also elsewhere on the board
+5V0_PA_3: X33.1; also elsewhere on the board
-3V3_SW: X18.1; also elsewhere on the board
-3V4: X24.1; also elsewhere on the board
-5V0_ADAR12: U36.5, X21.1; also elsewhere on the board
-5V0_ADAR34: U37.5, X20.1; also elsewhere on the board
-5V5_PA: X19.1; also elsewhere on the board
GND: U36.3, U36.6, U37.3, U37.6, X18.2, X18.3, X19.2, X19.3, X20.2, X20.3, X21.2, X21.3, X24.2, X24.3, X31.2, X31.3, X31.4, X32.2, X32.3, X32.4, X33.2, X33.3, X33.4, X36.2, X37.2, X38.2, X39.2, X40.2; also elsewhere on the board
N$U36_C1M: U36.4; also elsewhere on the board
N$U36_C1P: U36.2; also elsewhere on the board
N$U37_C1M: U37.4; also elsewhere on the board
N$U37_C1P: U37.2; also elsewhere on the board
PG_2V5_FPGA: X40.1; also elsewhere on the board
PG_3V3_ADTR: X38.1; also elsewhere on the board
PG_3V3_XO: X39.1; also elsewhere on the board

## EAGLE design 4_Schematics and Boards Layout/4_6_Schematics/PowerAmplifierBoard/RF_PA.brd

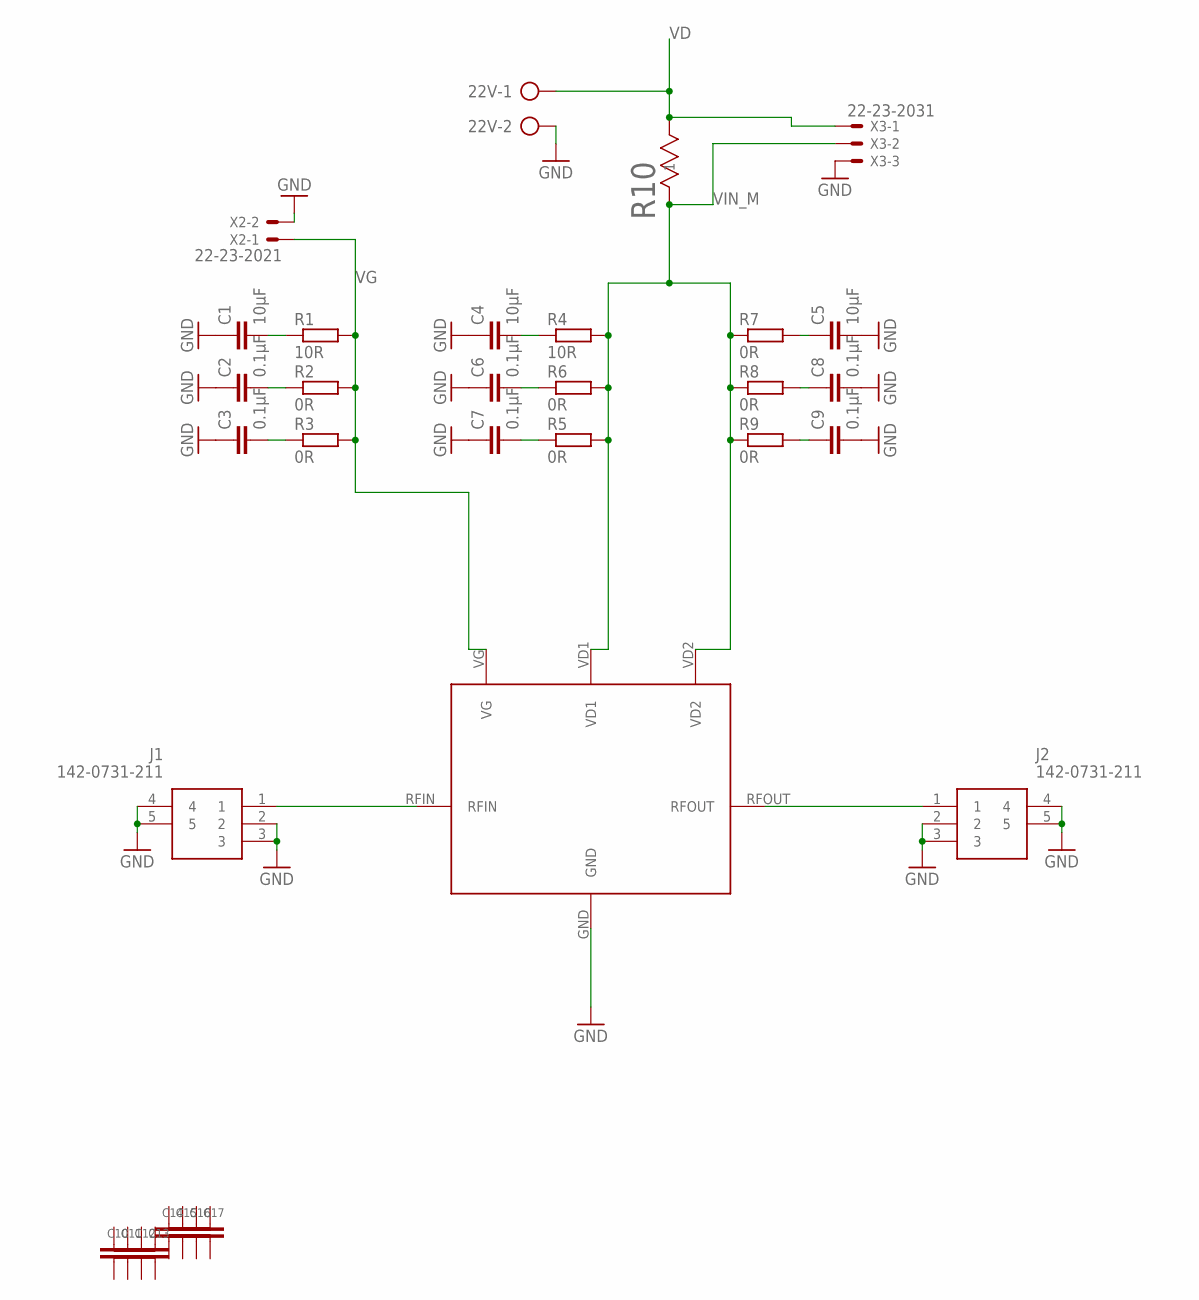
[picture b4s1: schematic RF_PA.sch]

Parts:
22V: AK300/2
C1, C4, C5, C10, C11, C12, C13, C14, C15, C16, C17: 10µF; C1206
C2, C3, C6, C7, C8, C9: 0.1µF; C0402
J1, J2: 142-0731-211; 1420731211
R1, R4: 10R; R0402
R2, R3, R5, R7, R8, R9: 0R; R0402
R6: 0R; R0603
R10: 5mR; WSL2816_VIS
U$1: QPA2962_B
X2: 22-23-2021
X3: 22-23-2031

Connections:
GND: 22V.2, C1.1, C2.1, C3.1, C4.1, C5.2, C6.1, C7.1, C8.2, C9.2, C10.2, C11.2, C12.2, C13.2, C14.2, C15.2, C16.2, C17.2, J1.2, J1.3, J1.4, J1.5, J2.2, J2.3, J2.4, J2.5, U$1.GND, X2.2, X3.3
unnamed: C3.2, R3.1
unnamed: J1.1, U$1.RFIN
unnamed: C1.2, R1.1
unnamed: C2.2, R2.1
unnamed: C4.2, R4.1
unnamed: C6.2, R6.1
unnamed: C7.2, R5.1
unnamed: J2.1, U$1.RFOUT
unnamed: C5.1, R7.2
unnamed: C8.1, R8.2
unnamed: C9.1, R9.2
VD: 22V.1, R10.2, X3.1
VG: R1.2, R2.2, R3.2, U$1.VG, X2.1
VIN_M: C10.1, C11.1, C12.1, C13.1, C14.1, C15.1, C16.1, C17.1, R4.2, R5.2, R6.2, R7.1, R8.1, R9.1, R10.1, U$1.VD1, U$1.VD2, X3.2

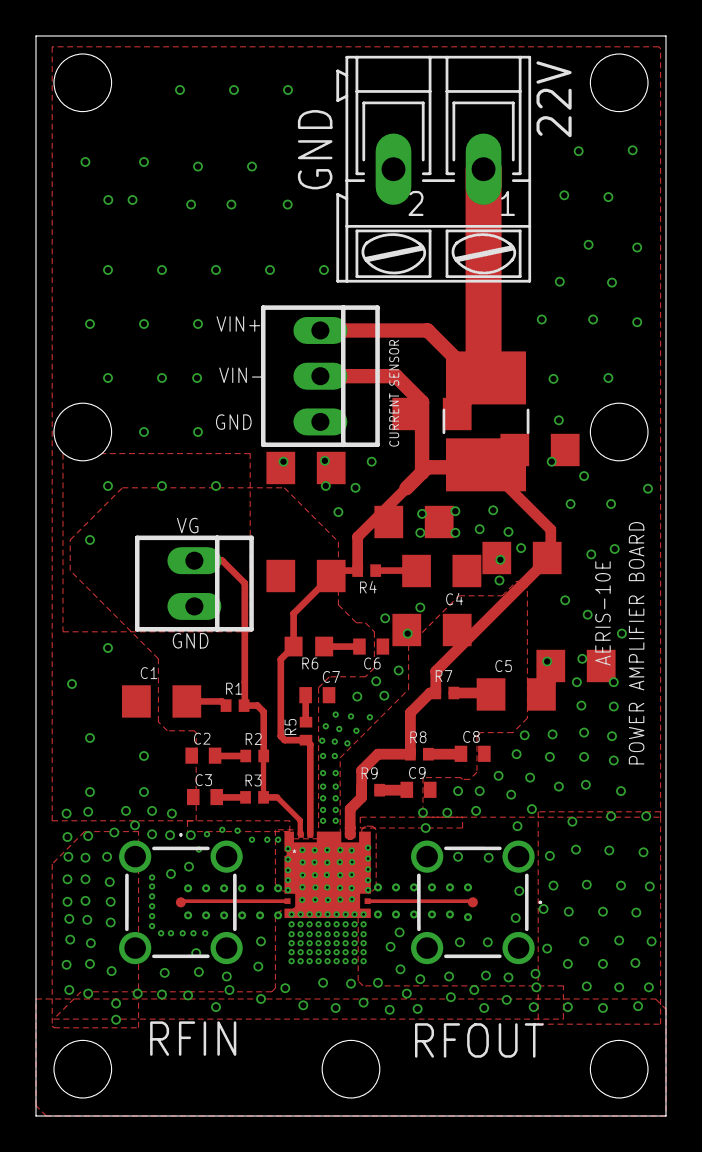
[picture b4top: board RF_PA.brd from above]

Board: 4 copper layers, 35.0 x 60.0 mm, 33 parts (0 on the bottom side), 15 nets.
